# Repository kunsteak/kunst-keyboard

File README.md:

# The Kunst Keyboard
Design idea inspired by Ben Vallack | [ZMK shield](https://github.com/kunsteak/zmk-config-kunst)

A custom 18-key keyboard:

Kunst Keymap:

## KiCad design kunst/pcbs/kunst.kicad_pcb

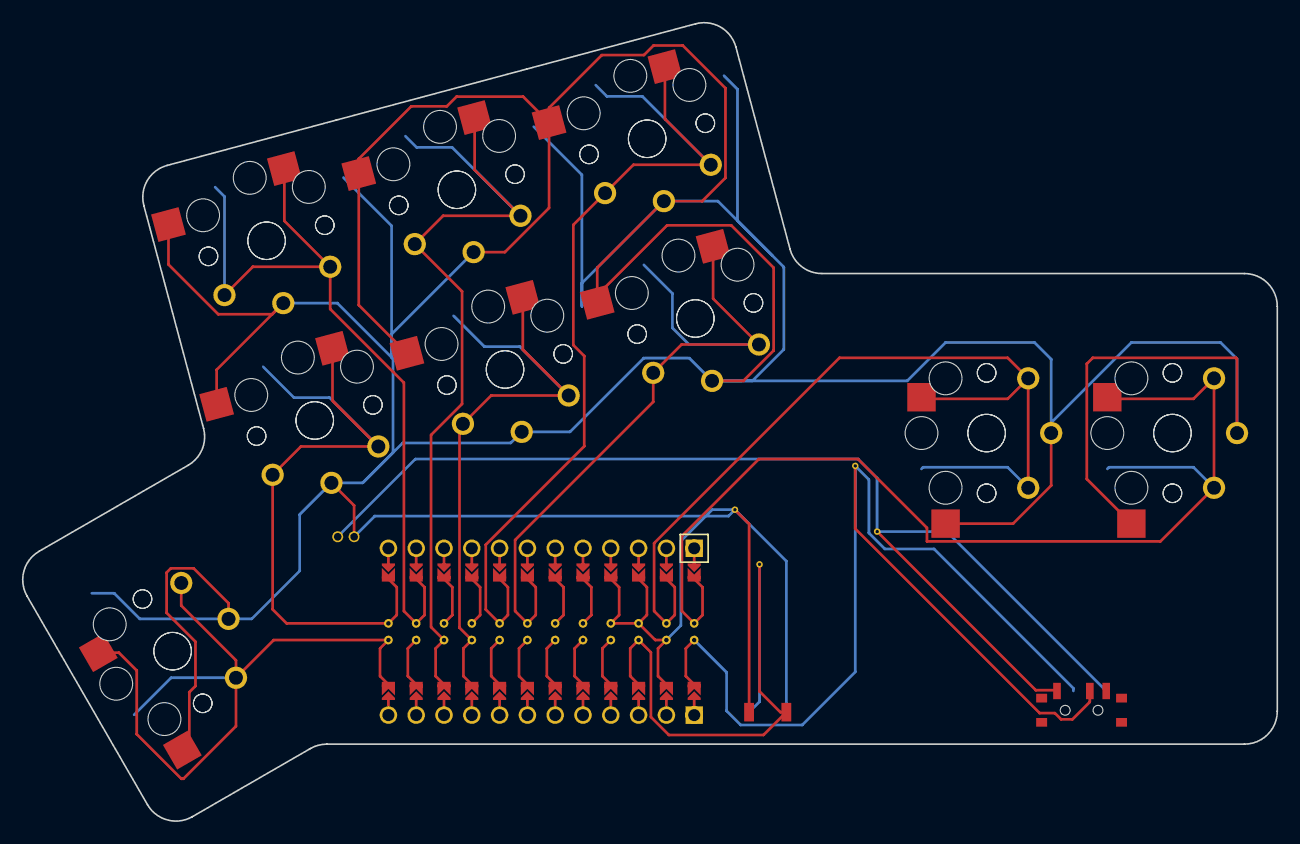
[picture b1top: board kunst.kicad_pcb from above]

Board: 2 copper layers, 114.6 x 72.9 mm, 19 parts (0 on the bottom side), 10 nets.

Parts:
MCU1: ProMicro
S1, S2, S3, S4, S5, S6, S7, S8, S9, S10, S11, S12, S13, S14, S15, S16, S17, S18: PG1350

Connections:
GND: MCU1.2, MCU1.21, MCU1.22, S1.2, S2.2, S3.2, S4.2, S5.2, S6.2, S7.2, S8.2, S9.2, S10.2, S11.2, S12.2, S13.2, S14.2, S15.2, S16.2, S17.2, S18.2
P0: MCU1.23, S15.1, S16.1
P1: MCU1.24, S17.1, S18.1
P4: MCU1.18, S11.1, S12.1
P5: MCU1.17, S13.1, S14.1
P8: MCU1.14, S5.1, S6.1
P9: MCU1.13, S3.1, S4.1
P10: MCU1.12, S1.1, S2.1
P14: MCU1.10, S9.1, S10.1
P15: MCU1.9, S7.1, S8.1

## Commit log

2022-08-07 primary
2022-08-07 added picture of keyboard
2022-08-07 Added Keymap PNG
